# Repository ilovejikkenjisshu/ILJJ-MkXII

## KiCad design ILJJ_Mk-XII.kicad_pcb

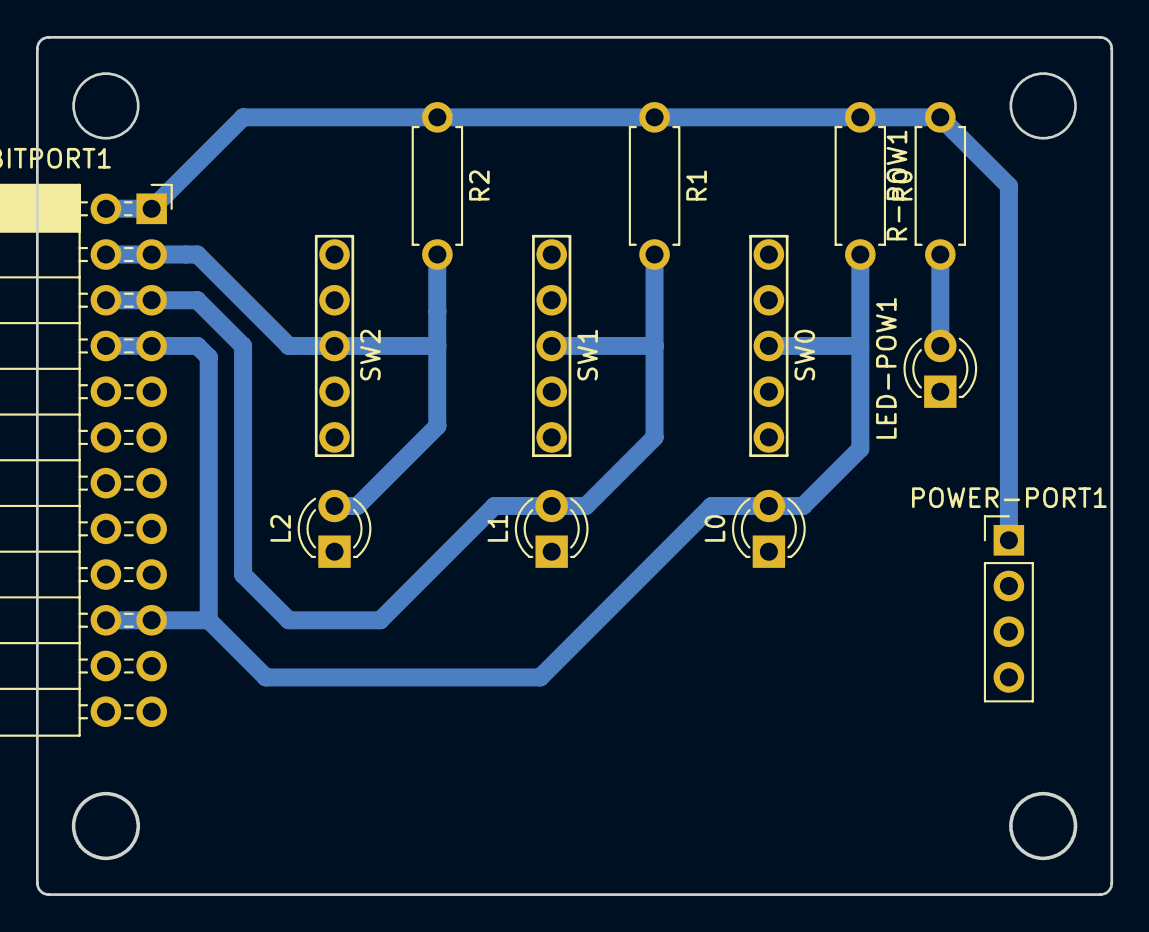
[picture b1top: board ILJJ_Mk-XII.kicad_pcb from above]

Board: 2 copper layers, 59.6 x 47.6 mm, 13 parts (0 on the bottom side), 6 nets.

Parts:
BITPORT1: Conn_02x12_Counter_Clockwise; PinSocket_2x12_P2.54mm_Horizontal
L0, L1, L2: LED; LED_D3.0mm
LED-POW1: LED; LED_D3.0mm
POWER-PORT1: Conn_01x04; PinHeader_1x04_P2.54mm_Vertical
R0, R1, R2: R; R_Axial_DIN0207_L6.3mm_D2.5mm_P7.62mm_Horizontal
R-POW1: R; R_Axial_DIN0207_L6.3mm_D2.5mm_P7.62mm_Horizontal
SW0, SW1, SW2: SW_SPDT; toggle_switch

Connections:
+5VA: BITPORT1.1, BITPORT1.2, POWER-PORT1.1, R0.1, R1.1, R2.1, R-POW1.2
/F0: BITPORT1.7, BITPORT1.8, BITPORT1.19, BITPORT1.20, L0.2, R0.2, SW0.2
/F1: BITPORT1.5, BITPORT1.6, L1.2, R1.2, SW1.2
/F2: BITPORT1.3, BITPORT1.4, L2.2, R2.2, SW2.2
GND: BITPORT1.23, BITPORT1.24, L0.1, L1.1, L2.1, LED-POW1.1, POWER-PORT1.4, SW0.3, SW1.3, SW2.3
unnamed: LED-POW1.2, R-POW1.1

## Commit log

2019-01-29 配線が一部(GND以外)完了
2019-01-29 add .gitignore and deleted some files
2019-01-29 外形、ネジ穴、GNDベタを追加
2019-01-29 [fix] 基板外形や配線の修正
2019-01-29 回路図の修正とGNDベタ入れ
2019-02-08 drlファイルを作成
2019-03-12 不要なファイルの削除
2019-03-12 update gitignore
2019-03-12 update 基板(?)データ
2019-03-12 穴経の調整とベタの塗り直し
2019-03-12 ガーバーファイルの出力に伴う修正
2019-03-12 穴径の再調整
